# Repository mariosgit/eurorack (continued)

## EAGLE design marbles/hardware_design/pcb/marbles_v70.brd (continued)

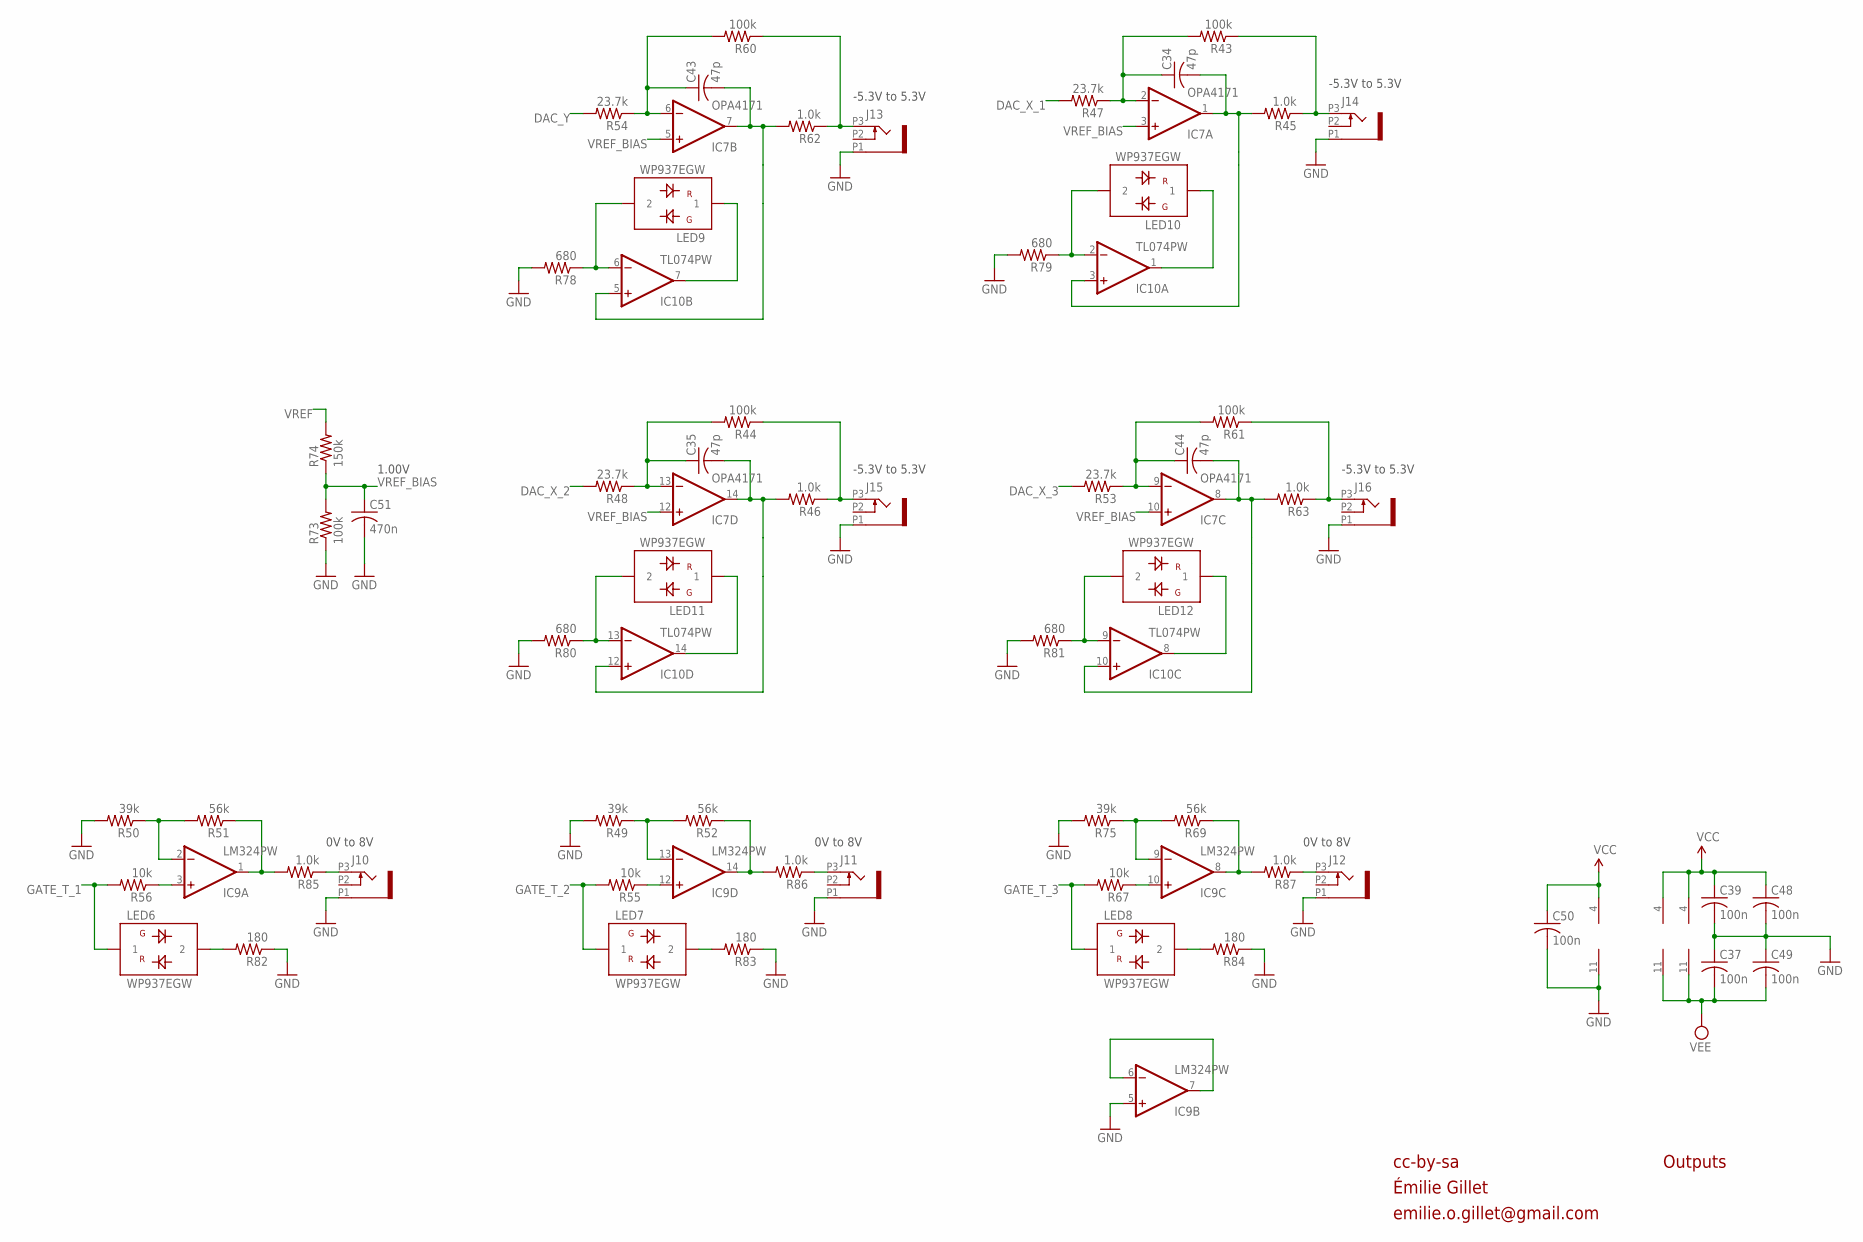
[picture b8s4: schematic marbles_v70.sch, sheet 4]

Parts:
C34, C35, C43, C44: 47p; C0603
C37, C39, C48, C49, C50: 100n; C0603
C51: 470n; C0603
IC7: OPA4171; TSSOP14_065
IC9: LM324PW; TSSOP14_065
IC10: TL074PW; TSSOP14_065
J10, J11, J12, J13, J14, J15, J16: PJ301_THONKICONN6; WQP_PJ_301M6
LED6, LED7, LED8, LED9, LED10, LED11, LED12: WP937EGW; LED3MM
R43, R44, R60, R61, R73: 100k; R0603
R45, R46, R62, R63, R85, R86, R87: 1.0k; R0603
R47, R48, R53, R54: 23.7k; R0603
R49, R50, R75: 39k; R0603
R51, R52, R69: 56k; R0603
R55, R56, R67: 10k; R0603
R74: 150k; R0603
R78, R79, R80, R81: 680; R0603
R82, R83, R84: 180; R0603

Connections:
DAC_X_1: R47.2; also elsewhere on the board
DAC_X_2: R48.2; also elsewhere on the board
DAC_X_3: R53.2; also elsewhere on the board
DAC_Y: R54.2; also elsewhere on the board
GATE_T_1: LED6.1, R56.2; also elsewhere on the board
GATE_T_2: LED7.1, R55.2; also elsewhere on the board
GATE_T_3: LED8.1, R67.2; also elsewhere on the board
GND: C37.1, C39.2, C48.2, C49.1, C50.2, C51.2, IC9.5 (+IN), IC9.11 (V-), J10.P1 (1), J11.P1 (1), J12.P1 (1), J13.P1 (1), J14.P1 (1), J15.P1 (1), J16.P1 (1), R49.2, R50.2, R73.1, R75.2, R78.2, R79.2, R80.2, R81.2, R82.1, R83.1, R84.1; also elsewhere on the board
unnamed: IC9.12 (+IN), R55.1
unnamed: IC9.1 (OUT), R51.1, R85.2
unnamed: J10.P3 (3), R85.1
unnamed: IC9.2 (-IN), R50.1, R51.2
unnamed: LED6.2, R82.2
unnamed: IC9.3 (+IN), R56.1
unnamed: IC9.6 (-IN), IC9.7 (OUT)
unnamed: IC9.14 (OUT), R52.1, R86.2
unnamed: IC9.13 (-IN), R49.1, R52.2
unnamed: IC9.10 (+IN), R67.1
unnamed: IC9.8 (OUT), R69.1, R87.2
unnamed: J11.P3 (3), R86.1
unnamed: J12.P3 (3), R87.1
unnamed: IC9.9 (-IN), R69.2, R75.1
unnamed: LED7.2, R83.2
unnamed: C43.2, IC7.7 (OUT), IC10.5 (+IN), R62.2
unnamed: LED8.2, R84.2
unnamed: J15.P3 (3), R44.1, R46.1
unnamed: J13.P3 (3), R60.1, R62.1
unnamed: C35.1, IC7.13 (-IN), R44.2, R48.1
unnamed: J16.P3 (3), R61.1, R63.1
unnamed: C44.1, IC7.9 (-IN), R53.1, R61.2
unnamed: C34.1, IC7.2 (-IN), R43.2, R47.1
unnamed: C43.1, IC7.6 (-IN), R54.1, R60.2
unnamed: J14.P3 (3), R43.1, R45.1
unnamed: IC10.6 (-IN), LED9.2, R78.1
unnamed: IC10.7 (OUT), LED9.1
unnamed: C34.2, IC7.1 (OUT), IC10.3 (+IN), R45.2
unnamed: IC10.2 (-IN), LED10.2, R79.1
unnamed: IC10.1 (OUT), LED10.1
unnamed: C35.2, IC7.14 (OUT), IC10.12 (+IN), R46.2
unnamed: IC10.13 (-IN), LED11.2, R80.1
unnamed: IC10.14 (OUT), LED11.1
unnamed: C44.2, IC7.8 (OUT), IC10.10 (+IN), R63.2
unnamed: IC10.9 (-IN), LED12.2, R81.1
unnamed: IC10.8 (OUT), LED12.1
VCC: C39.1, C48.1, C50.1, IC7.4 (V+), IC9.4 (V+), IC10.4 (V+); also elsewhere on the board
VEE: C37.2, C49.2, IC7.11 (V-), IC10.11 (V-); also elsewhere on the board
VREF: R74.2; also elsewhere on the board
VREF_BIAS: C51.1, IC7.3 (+IN), IC7.5 (+IN), IC7.10 (+IN), IC7.12 (+IN), R73.2, R74.1

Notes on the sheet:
-5.3V to 5.3V
0V to 8V
cc-by-sa
Outputs
1.00V
Émilie Gillet
emilie.o.gillet@gmail.com

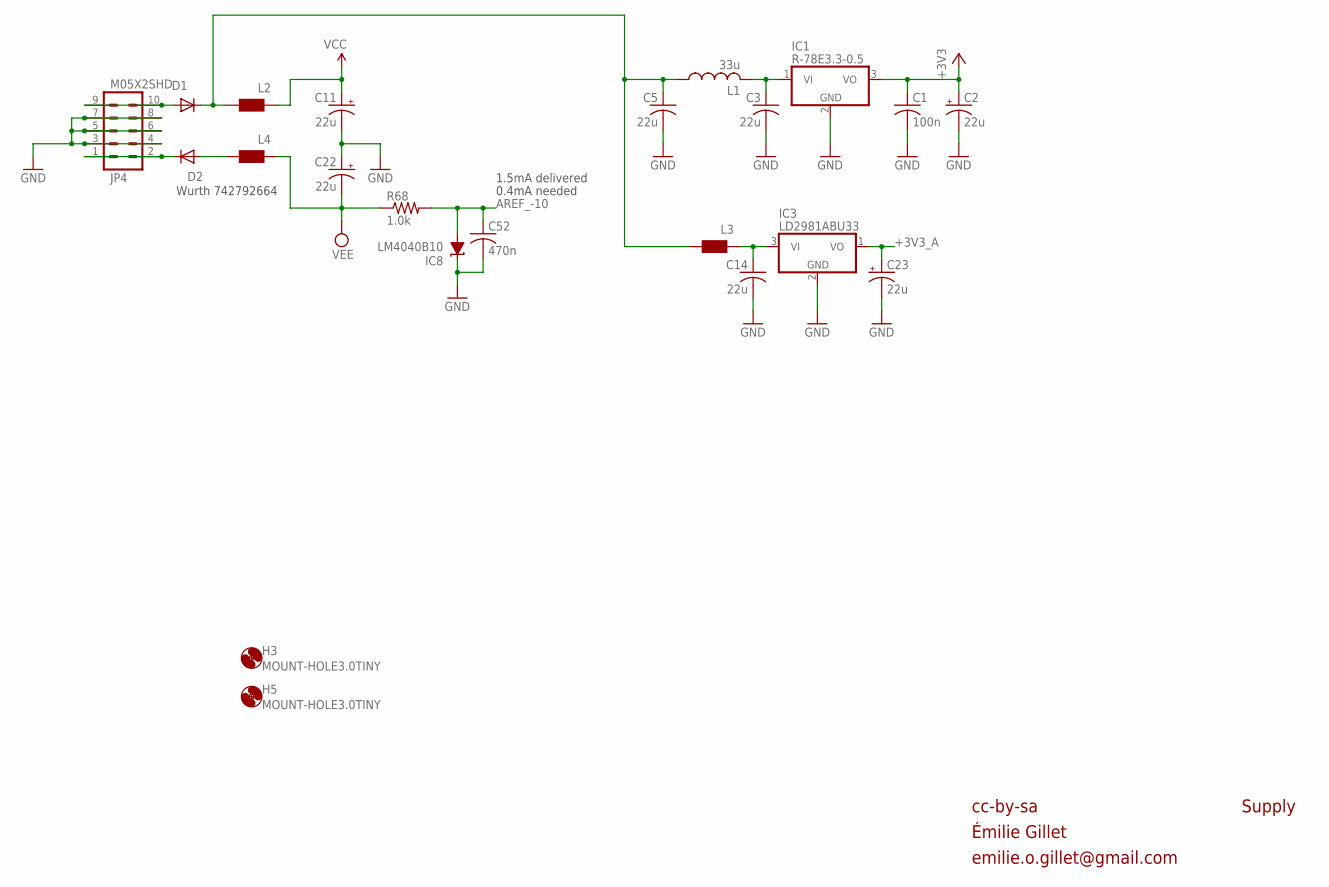
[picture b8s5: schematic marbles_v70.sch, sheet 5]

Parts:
C1: 100n; C0603
C2, C11, C22, C23: 22u; PANASONIC_C
C3, C5, C14: 22u; C1206
C52: 470n; C0603
D1, D2: 1N5819HW; SOD123
H3, H5: MOUNT-HOLE3.0TINY; 3,0TINY
IC1: R-78E3.3-0.5; WE78
IC3: LD2981ABU33; SOT89
IC8: LM4040B10; DBZ_R-PDSO-G3
JP4: M05X2SHD; 2X5-SHROUDED
L1: 33u; L2012C
L2, L3, L4: WE-CBF_0603; 0603
R68: 1.0k; R0603

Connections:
+3V3: C1.1, C2.+, IC1.3 (VO); also elsewhere on the board
+3V3_A: C23.+, IC3.1 (VO); also elsewhere on the board
AREF_-10: C52.1, IC8.2 (A), R68.2; also elsewhere on the board
GND: C1.2, C2.-, C3.2, C5.2, C11.-, C14.2, C22.+, C23.-, C52.2, IC1.2 (GND), IC3.2 (GND), IC8.1 (C), JP4.3, JP4.4, JP4.5, JP4.6, JP4.7, JP4.8; also elsewhere on the board
unnamed: C14.1, IC3.3 (VI), L3.1
unnamed: C5.1, D1.C, L1.1, L2.2, L3.2
unnamed: D2.A, L4.2
unnamed: C3.1, IC1.1 (VI), L1.2
unnamed: D1.A, JP4.9, JP4.10
unnamed: D2.C, JP4.1, JP4.2
VCC: C11.+, L2.1; also elsewhere on the board
VEE: C22.-, L4.1, R68.1; also elsewhere on the board

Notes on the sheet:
0.4mA needed
cc-by-sa
Supply
Wurth 742792664
1.5mA delivered
Émilie Gillet
emilie.o.gillet@gmail.com

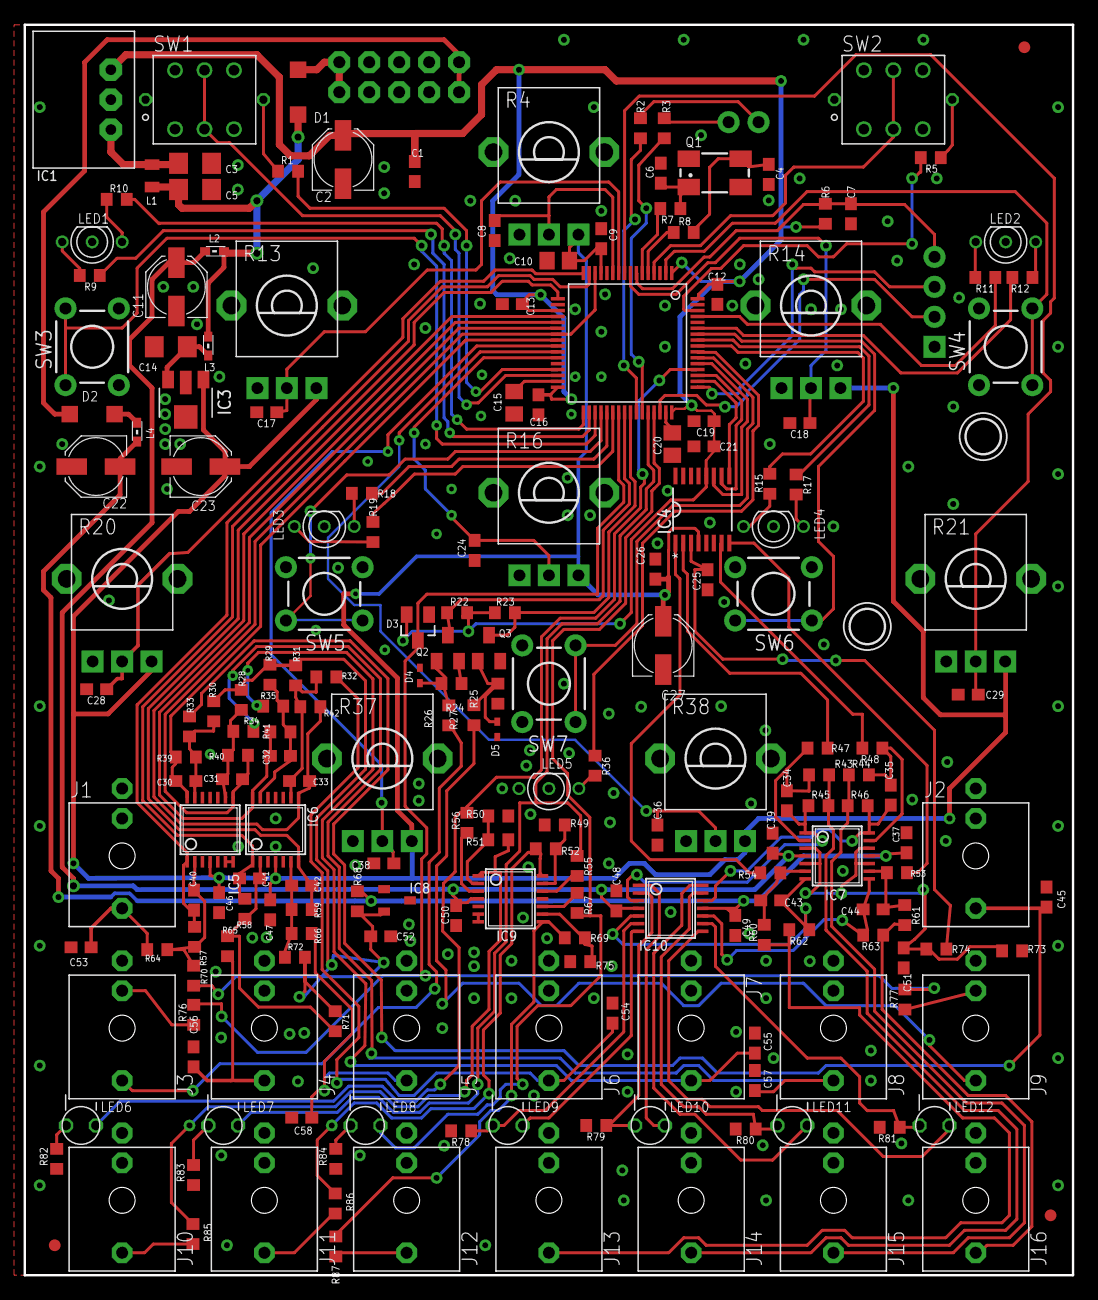
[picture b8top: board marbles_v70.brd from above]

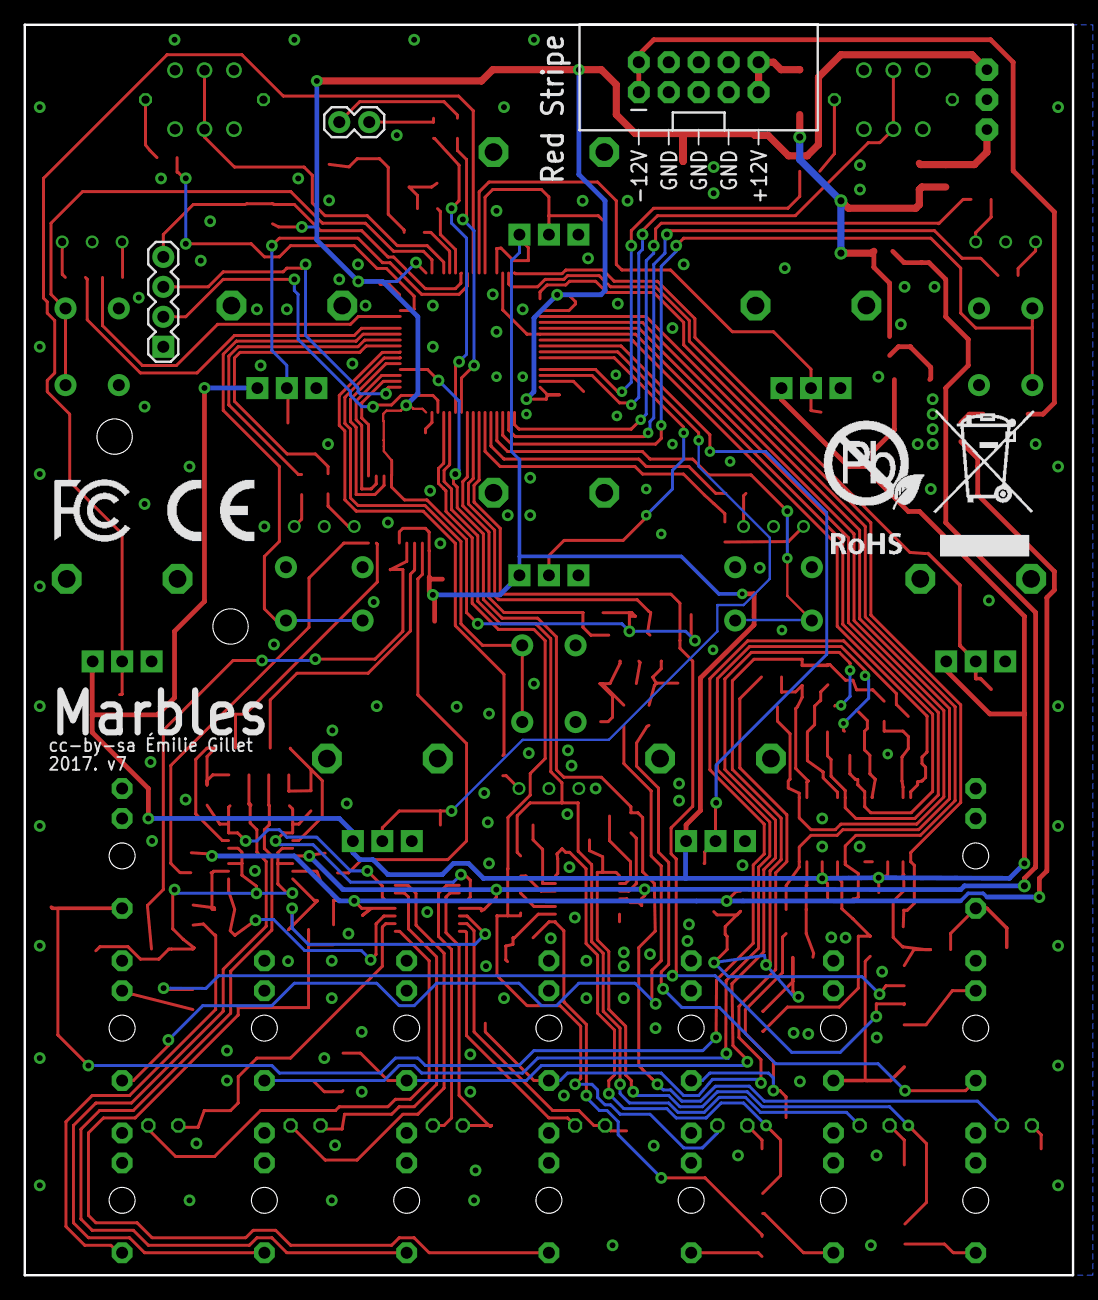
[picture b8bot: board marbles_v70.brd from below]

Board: 2 copper layers, 88.9 x 106.0 mm, 213 parts (6 on the bottom side), 141 nets.

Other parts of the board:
U$2: ROHS_BIG
U$4: CE_MEDIUM
U$5: FCC_MEDIUM
